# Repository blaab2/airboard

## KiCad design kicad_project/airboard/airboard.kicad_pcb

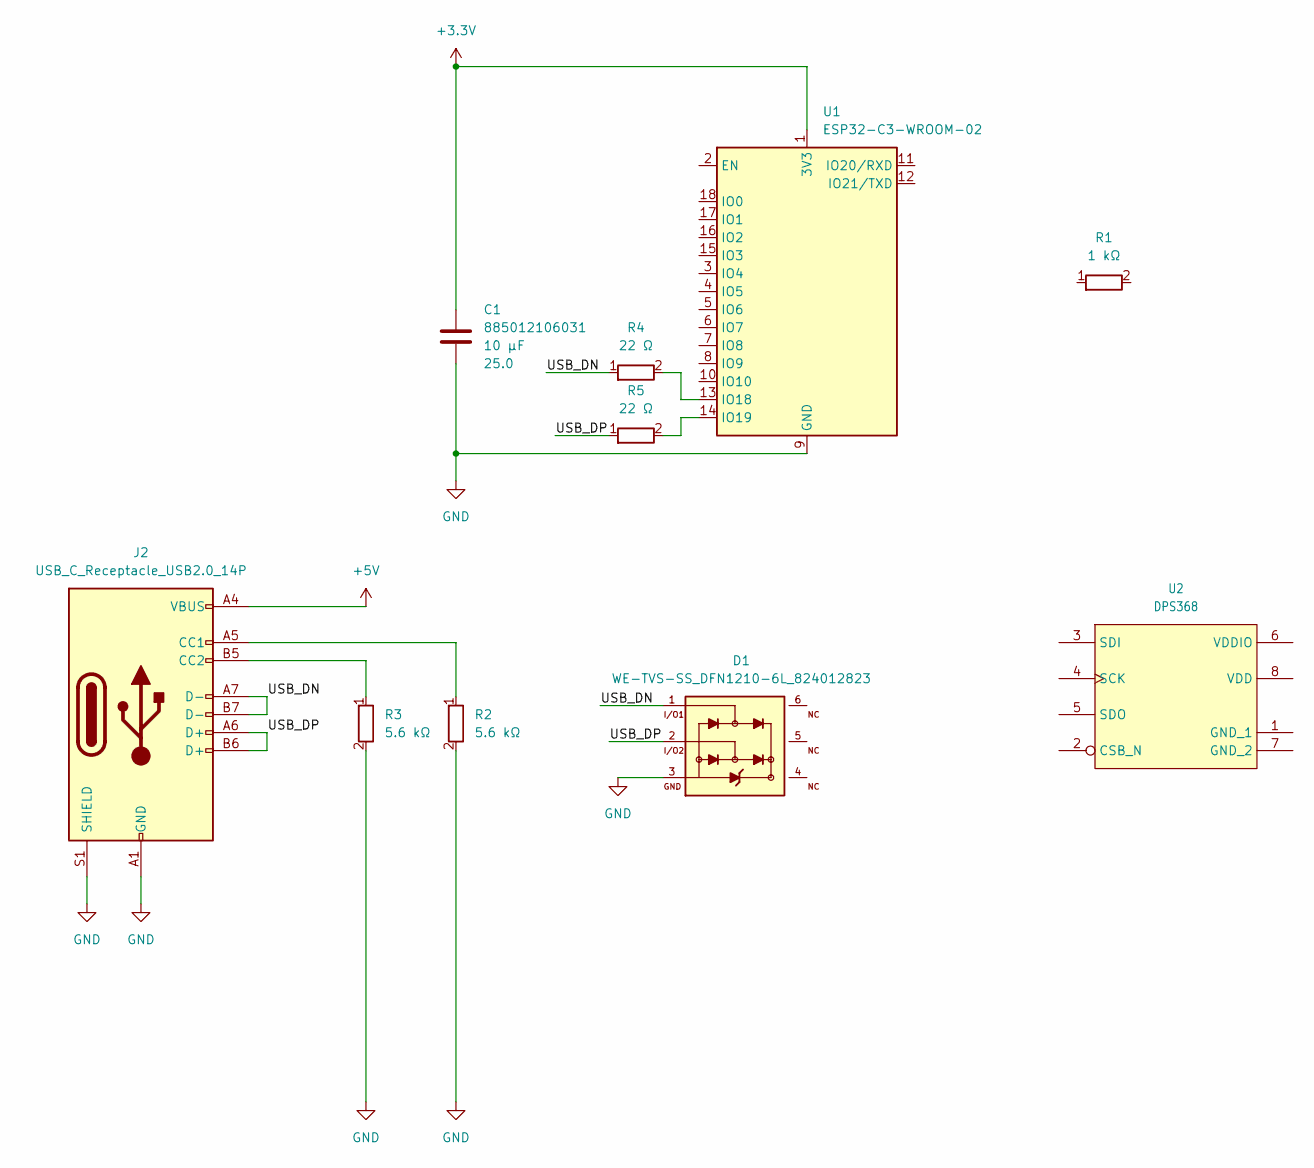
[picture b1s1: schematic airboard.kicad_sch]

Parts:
C1: 0603_Fl0.35_R_885012106031; C_Wurth_WCAP-CSGP-0603_Fl0.35_R; Voltage 25.0; Part Number 885012106031
D1: WE-TVS-SS_DFN1210-6L_824012823; WE-TVS_DFN1210-6L; MPN 824012823
J2: USB_C_Receptacle_USB2.0_14P; 629722000214; MPN 629722000214
R1: 0402_560112110012; R_Wurth_WRIS-RSKS-0402; MPN 560112110012
R2, R3: 0603_R_560112116017; R_Wurth_WRIS-RSKS-0603_R; Part Number 560112116017
R4, R5: 0603_R_560112116043; R_Wurth_WRIS-RSKS-0603_R; Part Number 560112116043
U1: ESP32-C3-WROOM-02
U2: DPS368; LGA8S145X65P2X4_200X250X110-V

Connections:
+3.3V: C1.1, U1.1 (3V3)
+5V: J2.A4 (VBUS), J2.A9 (VBUS), J2.B4 (VBUS), J2.B9 (VBUS)
/USB_DN: D1.1, J2.A7 (D-), J2.B7 (D-), R4.1
/USB_DP: D1.2, J2.A6 (D+), J2.B6 (D+), R5.1
GND: C1.2, D1.3, J2.A1 (GND), J2.A12 (GND), J2.B1 (GND), J2.B12 (GND), J2.S1 (SHIELD), R2.2, R3.2, U1.9 (GND), U1.19 (GND)
unnamed: J2.A5 (CC1), R2.1
unnamed: J2.B5 (CC2), R3.1
unnamed: R4.2, U1.13 (IO18)
unnamed: R5.2, U1.14 (IO19)

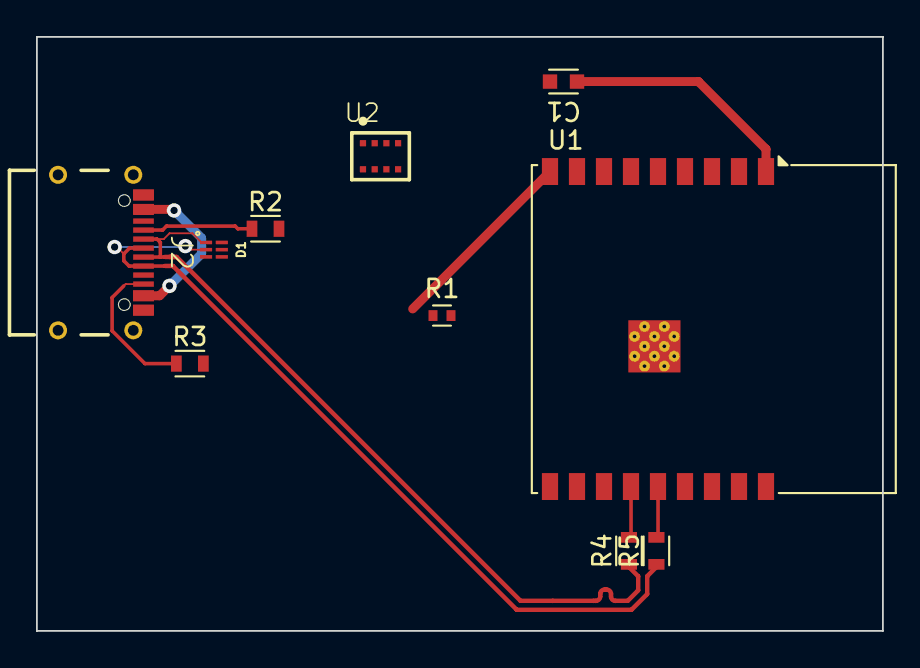
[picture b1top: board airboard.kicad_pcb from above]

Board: 2 copper layers, 47.0 x 33.0 mm, 10 parts (0 on the bottom side), 9 nets.

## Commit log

2026-01-04 Add initial KiCad library and symbol library table
    - Added a new subproject for the Wurth KiCad library.
    - Created a symbol library table for the airboard project.
    - Introduced a new template subproject for KiCad.
2026-01-04 feat(libs): add Resistor_Wurth_WRIS-RSKS to symbol library table
2026-01-05 feat: add commit message generation instructions for GitHub Copilot
2026-01-05 feat: add initial URL shortcut for ESP32-C3 DevKit schematic
2026-01-05 chore: update .gitignore to include jlcpcb directory
2026-01-05 feat(libs/wurth): add WE-TVS_DFN1210-6L footprint and import guide
2026-01-05 feat(libs/infineon): add DPS368 pressure sensor footprints and symbols
2026-01-05 feat(libs/wurth): add WE-TVS-SS_DFN1210-6L footprint zip file
2026-01-05 feat: add WR-TVS and WR-USB footprints and 3d models
2026-01-05 feat(kicad_project): add new libraries and update symbol and footprint tables
2026-01-05 feat(ci): add release-please workflow for automated releases
2026-01-05 feat(ci): add release-please workflow for automated releases (#3)
2026-01-05 chore(main): release 1.0.0
